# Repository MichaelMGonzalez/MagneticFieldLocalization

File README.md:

# MagneticFieldLocalization
The itensities of an indoor magnetic field may be used to aid localization of a mobile robot. This repository contains all the required files for an experiment to map and localize this field.

| Task | Status | Priority |Comments | Next Steps
| ---  | ---    | ---      | ---     | ---
| **3D CAD**
| 3D Phone Model | In-Progress | Medium | Test Model Printed | Re-print larger model
| 3D IR Wheel Encoder Model | In-Progress | Medium | Test Model Printed | Re-print larger model
| ---
| **Circuit**
| Make Board       | ORDERED     | HIGHEST | Waiting on Phone Model Test/ Schematic Verification | Solder
| Make Schemematic | Made Encoder| HIGHEST | Symbol/Phone Model Symbol/Voltage Divider | . | Label Resistor Values/Verify
| ---
| **Arduino Code**
| Main ino program    | Started | High | . | Draft
| Program Wheel Encoder | General Logic Drafted | Medium | Started to write header file| Test on hardware
| Differential Drive  | Classes made | Medium | Started to write header file| Test on hardware
| PID Controller      | Classes made | Low | . | Test on hardware
| Serial Communicator | Generation framework made | Medium | Shared Message Framework created | Lower baud rate
| ---
| **Android Code**
| GUI | Using sample code | Medium | . | Commit/Draft user flow chart
| Magnometer Sensor API | In-Progress | High | . | Read through API's
| Serial Communicator | External API's tested | High | Shared Message Framework created | Lower baud rate
| Localizer | Not Started | Very High | Depends on most everything else before we can begin | Finish everything else
| Network Module | Not Started | Medium/Low | It would be really nice to have some way to control the robot from a computer | ?
| ---
| **Python Data Viewers**
| Histogram Plotter | Made Script to plot velocities | Low | . | Generalize?
| Scatter Plot | Made Script to plot sensor voltages | Low | . | Generalize?
| ---

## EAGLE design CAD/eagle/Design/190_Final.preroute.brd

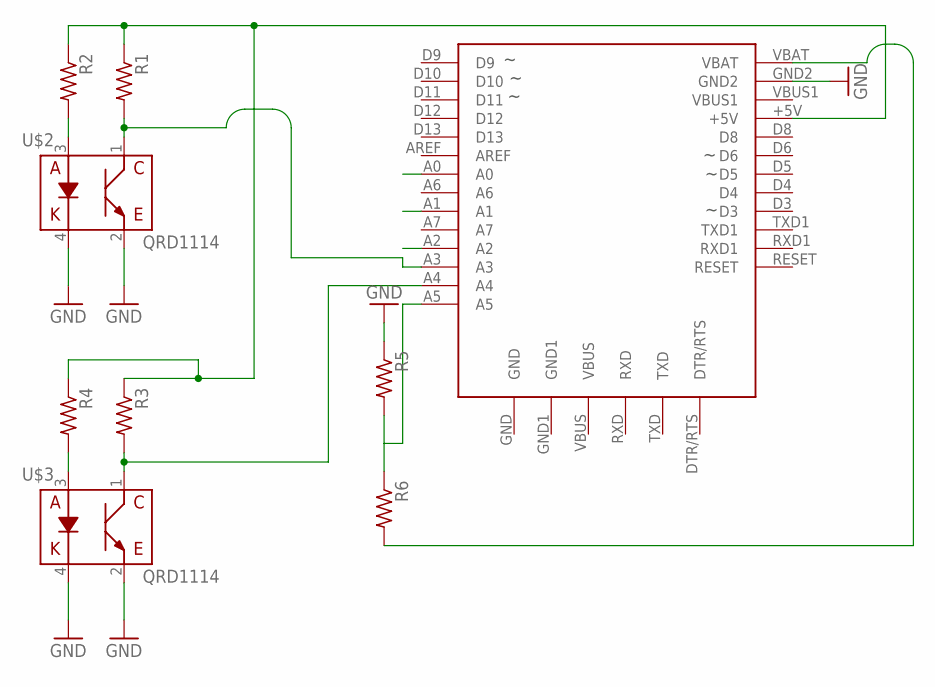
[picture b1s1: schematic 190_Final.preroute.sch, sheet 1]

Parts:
R1, R2, R3, R4, R5, R6: R-US_0204/7; 0204/7
U1_0_BRAIN: ADAFRUIT-PRO-TRINKET-5V-BOB; ADAFRUIT-PRO-TRINKET-5V
U$2, U$3: QRD1114

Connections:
+5V_0_BRAIN: R1.1, R2.1, R3.1, R4.1, U1_0_BRAIN.+5V; also elsewhere on the board
A0_0_BRAIN: U1_0_BRAIN.A0; also elsewhere on the board
A1_0_BRAIN: U1_0_BRAIN.A1; also elsewhere on the board
A2_0_BRAIN: U1_0_BRAIN.A2; also elsewhere on the board
A3_0_BRAIN: R1.2, U1_0_BRAIN.A3, U$2.1 (E)
A4_0_BRAIN: R3.2, U1_0_BRAIN.A4, U$3.1 (E)
A5_0_BRAIN: R5.2, R6.1, U1_0_BRAIN.A5
A6_0_BRAIN: U1_0_BRAIN.A6
A7_0_BRAIN: U1_0_BRAIN.A7
AREF_0_BRAIN: U1_0_BRAIN.AREF
D3_0_BRAIN: U1_0_BRAIN.D3; also elsewhere on the board
D4_0_BRAIN: U1_0_BRAIN.D4; also elsewhere on the board
D5_0_BRAIN: U1_0_BRAIN.D5; also elsewhere on the board
D6_0_BRAIN: U1_0_BRAIN.D6; also elsewhere on the board
D8_0_BRAIN: U1_0_BRAIN.D8; also elsewhere on the board
D9_0_BRAIN: U1_0_BRAIN.D9; also elsewhere on the board
D10_0_BRAIN: U1_0_BRAIN.D10; also elsewhere on the board
D11_0_BRAIN: U1_0_BRAIN.D11; also elsewhere on the board
D12_0_BRAIN: U1_0_BRAIN.D12; also elsewhere on the board
D13_0_BRAIN: U1_0_BRAIN.D13; also elsewhere on the board
DTR/RTS_0_BRAIN: U1_0_BRAIN.DTR/RTS
GND_0_BRAIN: R5.1, U1_0_BRAIN.GND, U1_0_BRAIN.GND1, U1_0_BRAIN.GND2, U$2.2 (C), U$2.4 (K), U$3.2 (C), U$3.4 (K); also elsewhere on the board
unnamed: R2.2, U$2.3 (A)
unnamed: R4.2, U$3.3 (A)
POS_1_BATTERY: R6.2, U1_0_BRAIN.VBAT; also elsewhere on the board
RESET_0_BRAIN: U1_0_BRAIN.RESET
RXD1_0_BRAIN: U1_0_BRAIN.RXD1
RXD_0_BRAIN: U1_0_BRAIN.RXD
TXD1_0_BRAIN: U1_0_BRAIN.TXD1
TXD_0_BRAIN: U1_0_BRAIN.TXD
VBUS1_0_BRAIN: U1_0_BRAIN.VBUS1
VBUS_0_BRAIN: U1_0_BRAIN.VBUS

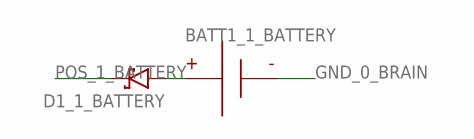
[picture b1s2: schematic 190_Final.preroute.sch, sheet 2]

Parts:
BATT1_1_BATTERY: BATTERY-9V-VERTICAL; BATTERY_9V_KEYSTONE_968
D1_1_BATTERY: RESOLVED-DIODE-SCHOTTKY_TH-DO-41-AND-DO-204AL; DIOAD1125W78L520D270_HS; MPN 1N5817

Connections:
GND_0_BRAIN: BATT1_1_BATTERY.N; also elsewhere on the board
unnamed: BATT1_1_BATTERY.P, D1_1_BATTERY.A
POS_1_BATTERY: D1_1_BATTERY.C; also elsewhere on the board

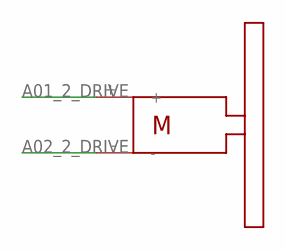
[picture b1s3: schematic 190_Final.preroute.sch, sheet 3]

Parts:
R_2_DRIVE: SOLARBOTICS_GM2; SOLARBOTICS_G2

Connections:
A01_2_DRIVE: R_2_DRIVE.+; also elsewhere on the board
A02_2_DRIVE: R_2_DRIVE.-; also elsewhere on the board

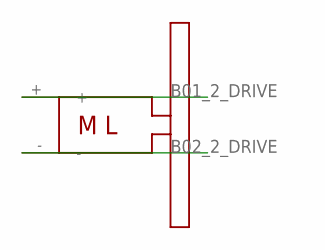
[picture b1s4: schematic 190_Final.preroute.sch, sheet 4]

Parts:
L_2_DRIVE: SOLARBOTICS_GM2_LEFT; SOLARBOTICS_G2_LEFT

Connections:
B01_2_DRIVE: L_2_DRIVE.+; also elsewhere on the board
B02_2_DRIVE: L_2_DRIVE.-; also elsewhere on the board

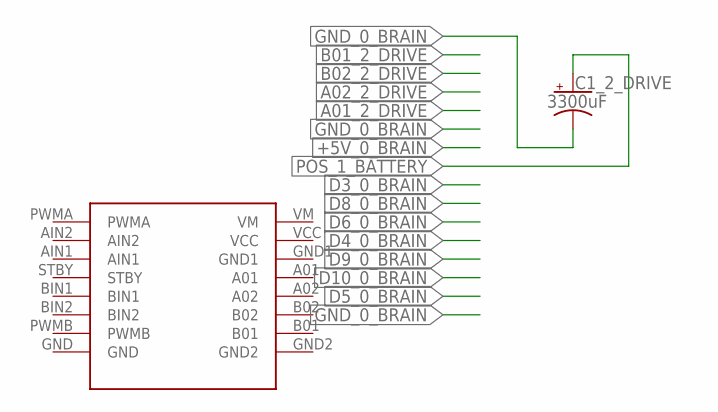
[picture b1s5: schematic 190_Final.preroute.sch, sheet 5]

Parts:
C1_2_DRIVE: 3300uF; CAPPRD750W80D1600H2200P; MPN ECA-1EM332
DRVR_2_DRIVE: SPARKFUN_DUAL_MOTOR_DRIVER-BOB; SPARKFUN_DUAL_MOTOR_DRIVER

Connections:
+5V_0_BRAIN: DRVR_2_DRIVE.VCC; also elsewhere on the board
A01_2_DRIVE: DRVR_2_DRIVE.A01; also elsewhere on the board
A02_2_DRIVE: DRVR_2_DRIVE.A02; also elsewhere on the board
B01_2_DRIVE: DRVR_2_DRIVE.B01; also elsewhere on the board
B02_2_DRIVE: DRVR_2_DRIVE.B02; also elsewhere on the board
D3_0_BRAIN: DRVR_2_DRIVE.PWMA; also elsewhere on the board
D4_0_BRAIN: DRVR_2_DRIVE.STBY; also elsewhere on the board
D5_0_BRAIN: DRVR_2_DRIVE.PWMB; also elsewhere on the board
D6_0_BRAIN: DRVR_2_DRIVE.AIN1; also elsewhere on the board
D8_0_BRAIN: DRVR_2_DRIVE.AIN2; also elsewhere on the board
D9_0_BRAIN: DRVR_2_DRIVE.BIN1; also elsewhere on the board
D10_0_BRAIN: DRVR_2_DRIVE.BIN2; also elsewhere on the board
GND_0_BRAIN: C1_2_DRIVE.2 (-), DRVR_2_DRIVE.GND, DRVR_2_DRIVE.GND1, DRVR_2_DRIVE.GND2; also elsewhere on the board
POS_1_BATTERY: C1_2_DRIVE.1 (+), DRVR_2_DRIVE.VM; also elsewhere on the board

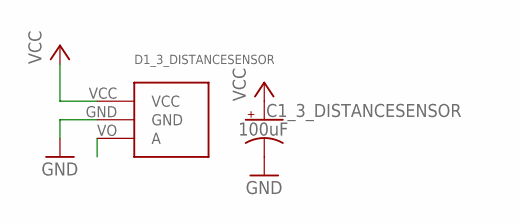
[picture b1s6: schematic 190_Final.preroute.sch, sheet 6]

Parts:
C1_3_DISTANCESENSOR: 100uF; CAPPRD250W80D630H1220P; MPN ECA-1EM101
D1_3_DISTANCESENSOR: ANALOG_DISTANCE_SENSOR-GLUE; ANALOG_DISTANCE_SENSOR_GLUE_MOUNT

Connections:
+5V_0_BRAIN: C1_3_DISTANCESENSOR.1 (+), D1_3_DISTANCESENSOR.VCC; also elsewhere on the board
A0_0_BRAIN: D1_3_DISTANCESENSOR.VO (A); also elsewhere on the board
GND_0_BRAIN: C1_3_DISTANCESENSOR.2 (-), D1_3_DISTANCESENSOR.GND; also elsewhere on the board

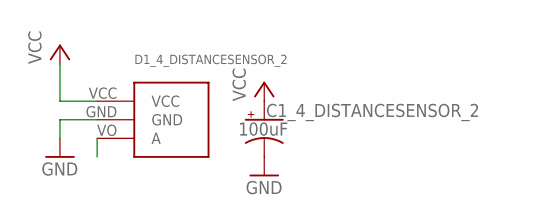
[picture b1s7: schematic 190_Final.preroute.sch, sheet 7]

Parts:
C1_4_DISTANCESENSOR_2: 100uF; CAPPRD250W80D630H1220P; MPN ECA-1EM101
D1_4_DISTANCESENSOR_2: ANALOG_DISTANCE_SENSOR-GLUE; ANALOG_DISTANCE_SENSOR_GLUE_MOUNT

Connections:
+5V_0_BRAIN: C1_4_DISTANCESENSOR_2.1 (+), D1_4_DISTANCESENSOR_2.VCC; also elsewhere on the board
A1_0_BRAIN: D1_4_DISTANCESENSOR_2.VO (A); also elsewhere on the board
GND_0_BRAIN: C1_4_DISTANCESENSOR_2.2 (-), D1_4_DISTANCESENSOR_2.GND; also elsewhere on the board

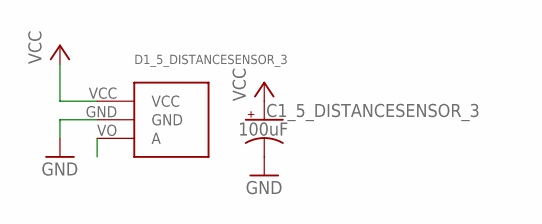
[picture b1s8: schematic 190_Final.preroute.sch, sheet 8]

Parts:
C1_5_DISTANCESENSOR_3: 100uF; CAPPRD250W80D630H1220P; MPN ECA-1EM101
D1_5_DISTANCESENSOR_3: ANALOG_DISTANCE_SENSOR-GLUE; ANALOG_DISTANCE_SENSOR_GLUE_MOUNT

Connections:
+5V_0_BRAIN: C1_5_DISTANCESENSOR_3.1 (+), D1_5_DISTANCESENSOR_3.VCC; also elsewhere on the board
A2_0_BRAIN: D1_5_DISTANCESENSOR_3.VO (A); also elsewhere on the board
GND_0_BRAIN: C1_5_DISTANCESENSOR_3.2 (-), D1_5_DISTANCESENSOR_3.GND; also elsewhere on the board

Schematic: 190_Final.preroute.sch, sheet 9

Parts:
U1_6_CASTER: CASTERADAFRUIT-3/4IN; ADAFRUIT-3/4IN-CASTER

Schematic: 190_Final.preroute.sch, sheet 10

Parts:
U1_7_CASTER_2: CASTERADAFRUIT-3/4IN; ADAFRUIT-3/4IN-CASTER

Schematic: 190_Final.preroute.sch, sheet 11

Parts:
LED1_8_LED: LED5MM
R1_8_LED: 330; RESAD770W45L370D210_HS; MPN CFR-12JB-52-330R

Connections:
D11_0_BRAIN: LED1_8_LED.A; also elsewhere on the board
GND_0_BRAIN: R1_8_LED.2; also elsewhere on the board
unnamed: LED1_8_LED.K (C), R1_8_LED.1

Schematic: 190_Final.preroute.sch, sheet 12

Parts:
LED1_9_LED_2: LED5MM
R1_9_LED_2: 330; RESAD770W45L370D210_HS; MPN CFR-12JB-52-330R

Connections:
D12_0_BRAIN: LED1_9_LED_2.A; also elsewhere on the board
GND_0_BRAIN: R1_9_LED_2.2; also elsewhere on the board
unnamed: LED1_9_LED_2.K (C), R1_9_LED_2.1

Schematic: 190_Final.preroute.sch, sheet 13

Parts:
B1_10_BUTTON: BUTTON-TACTILE-ROUND; BUTTON-TACTILE-ROUND-ADAFRUIT1009

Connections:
D13_0_BRAIN: B1_10_BUTTON.P; also elsewhere on the board
GND_0_BRAIN: B1_10_BUTTON.S; also elsewhere on the board

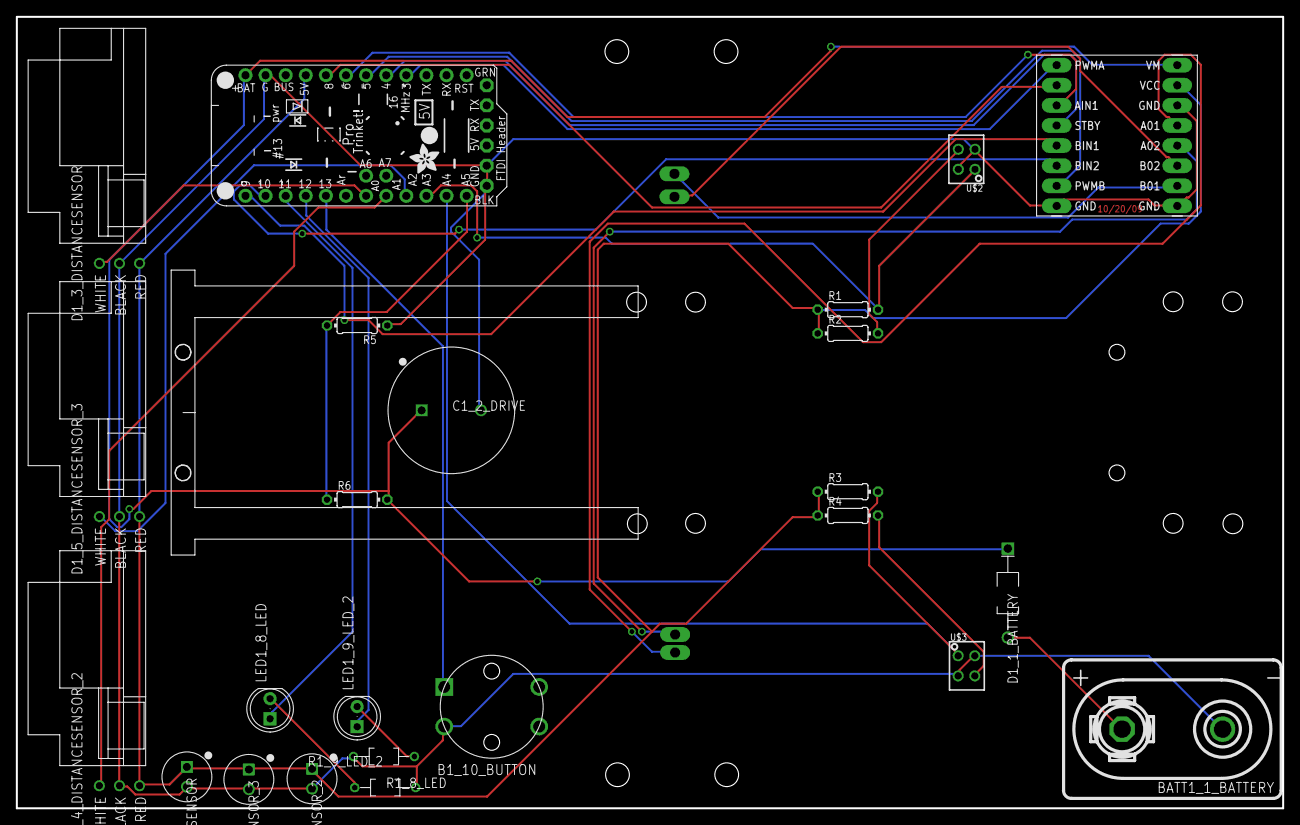
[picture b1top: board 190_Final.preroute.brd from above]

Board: 2 copper layers, 160.0 x 100.0 mm, 30 parts (0 on the bottom side), 28 nets.

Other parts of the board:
U$1: PHONE_STAND
U$4: IRSTAND

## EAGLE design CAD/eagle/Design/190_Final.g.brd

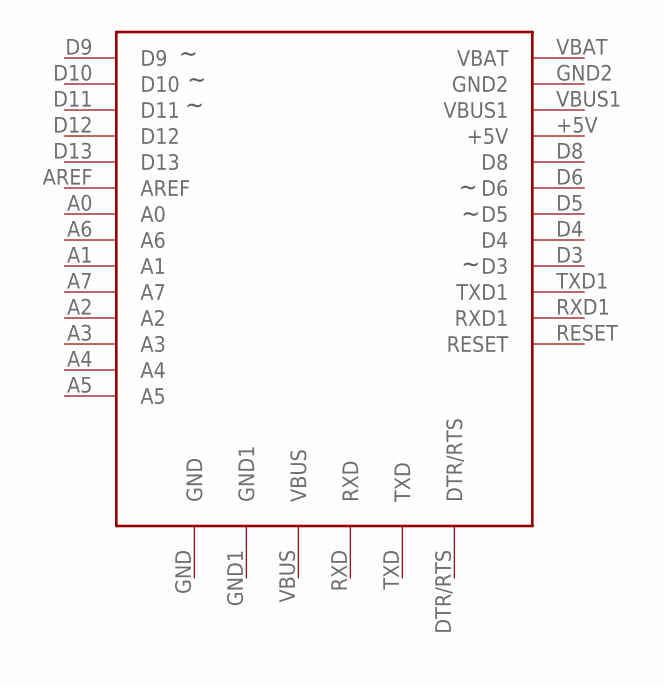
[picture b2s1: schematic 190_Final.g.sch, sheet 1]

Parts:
U1_0_brain: ADAFRUIT-PRO-TRINKET-5V-BOB; ADAFRUIT-PRO-TRINKET-5V

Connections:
+5V_0_brain: U1_0_brain.+5V; also elsewhere on the board
A0_0_brain: U1_0_brain.A0; also elsewhere on the board
A1_0_brain: U1_0_brain.A1; also elsewhere on the board
A2_0_brain: U1_0_brain.A2; also elsewhere on the board
A3_0_brain: U1_0_brain.A3
A4_0_brain: U1_0_brain.A4
A5_0_brain: U1_0_brain.A5
A6_0_brain: U1_0_brain.A6
A7_0_brain: U1_0_brain.A7
AREF_0_brain: U1_0_brain.AREF
D3_0_brain: U1_0_brain.D3; also elsewhere on the board
D4_0_brain: U1_0_brain.D4; also elsewhere on the board
D5_0_brain: U1_0_brain.D5; also elsewhere on the board
D6_0_brain: U1_0_brain.D6; also elsewhere on the board
D8_0_brain: U1_0_brain.D8; also elsewhere on the board
D9_0_brain: U1_0_brain.D9; also elsewhere on the board
D10_0_brain: U1_0_brain.D10; also elsewhere on the board
D11_0_brain: U1_0_brain.D11; also elsewhere on the board
D12_0_brain: U1_0_brain.D12; also elsewhere on the board
D13_0_brain: U1_0_brain.D13; also elsewhere on the board
DTR/RTS_0_brain: U1_0_brain.DTR/RTS
GND_0_brain: U1_0_brain.GND, U1_0_brain.GND1, U1_0_brain.GND2; also elsewhere on the board
POS_1_battery: U1_0_brain.VBAT; also elsewhere on the board
RESET_0_brain: U1_0_brain.RESET
RXD1_0_brain: U1_0_brain.RXD1
RXD_0_brain: U1_0_brain.RXD
TXD1_0_brain: U1_0_brain.TXD1
TXD_0_brain: U1_0_brain.TXD
VBUS1_0_brain: U1_0_brain.VBUS1
VBUS_0_brain: U1_0_brain.VBUS

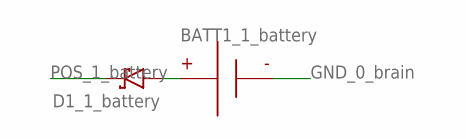
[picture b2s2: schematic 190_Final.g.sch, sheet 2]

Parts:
BATT1_1_battery: BATTERY-9V-VERTICAL; BATTERY_9V_KEYSTONE_968

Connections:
GND_0_brain: BATT1_1_battery.N; also elsewhere on the board

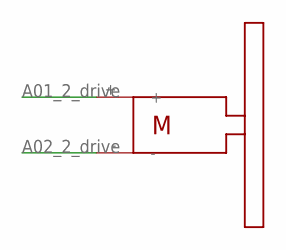
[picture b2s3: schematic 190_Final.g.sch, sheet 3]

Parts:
R_2_drive: SOLARBOTICS_GM2; SOLARBOTICS_G2

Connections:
A01_2_drive: R_2_drive.+; also elsewhere on the board
A02_2_drive: R_2_drive.-; also elsewhere on the board

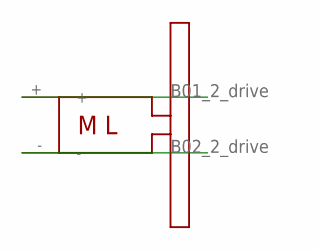
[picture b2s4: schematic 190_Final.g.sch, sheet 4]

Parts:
L_2_drive: SOLARBOTICS_GM2_LEFT; SOLARBOTICS_G2_LEFT

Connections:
B01_2_drive: L_2_drive.+; also elsewhere on the board
B02_2_drive: L_2_drive.-; also elsewhere on the board

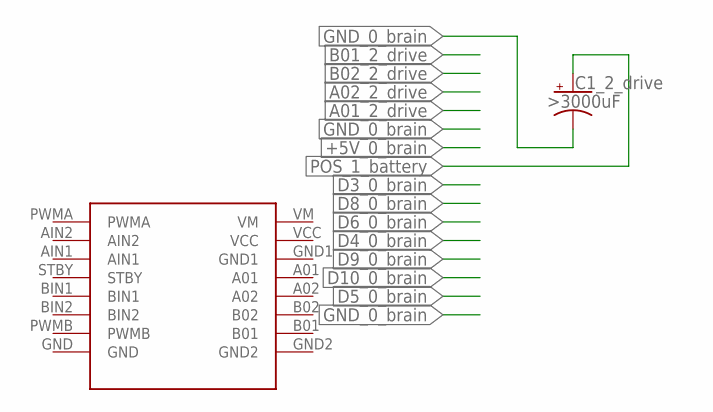
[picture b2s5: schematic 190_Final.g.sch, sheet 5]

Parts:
DRVR_2_drive: SPARKFUN_DUAL_MOTOR_DRIVER-BOB; SPARKFUN_DUAL_MOTOR_DRIVER

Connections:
+5V_0_brain: DRVR_2_drive.VCC; also elsewhere on the board
A01_2_drive: DRVR_2_drive.A01; also elsewhere on the board
A02_2_drive: DRVR_2_drive.A02; also elsewhere on the board
B01_2_drive: DRVR_2_drive.B01; also elsewhere on the board
B02_2_drive: DRVR_2_drive.B02; also elsewhere on the board
D3_0_brain: DRVR_2_drive.PWMA; also elsewhere on the board
D4_0_brain: DRVR_2_drive.STBY; also elsewhere on the board
D5_0_brain: DRVR_2_drive.PWMB; also elsewhere on the board
D6_0_brain: DRVR_2_drive.AIN1; also elsewhere on the board
D8_0_brain: DRVR_2_drive.AIN2; also elsewhere on the board
D9_0_brain: DRVR_2_drive.BIN1; also elsewhere on the board
D10_0_brain: DRVR_2_drive.BIN2; also elsewhere on the board
GND_0_brain: DRVR_2_drive.GND, DRVR_2_drive.GND1, DRVR_2_drive.GND2; also elsewhere on the board
POS_1_battery: DRVR_2_drive.VM; also elsewhere on the board

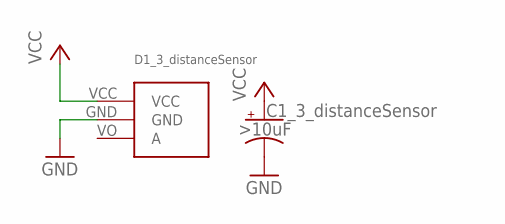
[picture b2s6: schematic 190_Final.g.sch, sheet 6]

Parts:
D1_3_distanceSensor: ANALOG_DISTANCE_SENSOR-GLUE; ANALOG_DISTANCE_SENSOR_GLUE_MOUNT

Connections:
+5V_0_brain: D1_3_distanceSensor.VCC; also elsewhere on the board
A0_0_brain: D1_3_distanceSensor.VO (A); also elsewhere on the board
GND_0_brain: D1_3_distanceSensor.GND; also elsewhere on the board

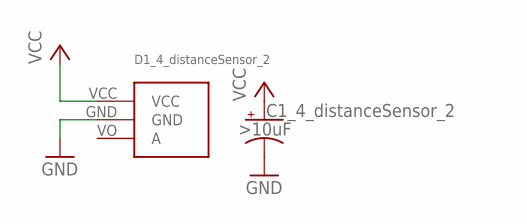
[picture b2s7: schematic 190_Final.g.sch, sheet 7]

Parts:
D1_4_distanceSensor_2: ANALOG_DISTANCE_SENSOR-GLUE; ANALOG_DISTANCE_SENSOR_GLUE_MOUNT

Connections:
+5V_0_brain: D1_4_distanceSensor_2.VCC; also elsewhere on the board
A1_0_brain: D1_4_distanceSensor_2.VO (A); also elsewhere on the board
GND_0_brain: D1_4_distanceSensor_2.GND; also elsewhere on the board

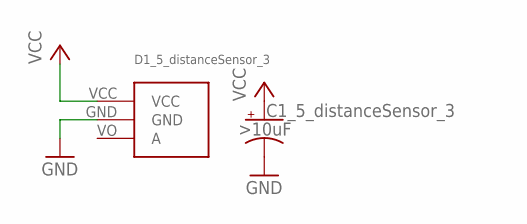
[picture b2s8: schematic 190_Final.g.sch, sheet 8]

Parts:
D1_5_distanceSensor_3: ANALOG_DISTANCE_SENSOR-GLUE; ANALOG_DISTANCE_SENSOR_GLUE_MOUNT

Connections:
+5V_0_brain: D1_5_distanceSensor_3.VCC; also elsewhere on the board
A2_0_brain: D1_5_distanceSensor_3.VO (A); also elsewhere on the board
GND_0_brain: D1_5_distanceSensor_3.GND; also elsewhere on the board

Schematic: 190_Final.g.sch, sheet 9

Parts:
u1_6_caster: CASTERADAFRUIT-3/4IN; ADAFRUIT-3/4IN-CASTER

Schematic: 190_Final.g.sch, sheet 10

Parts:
u1_7_caster_2: CASTERADAFRUIT-3/4IN; ADAFRUIT-3/4IN-CASTER

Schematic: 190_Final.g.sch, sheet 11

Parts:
LED1_8_led: LED5MM

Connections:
D11_0_brain: LED1_8_led.A; also elsewhere on the board

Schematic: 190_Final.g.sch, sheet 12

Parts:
LED1_9_led_2: LED5MM

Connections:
D12_0_brain: LED1_9_led_2.A; also elsewhere on the board

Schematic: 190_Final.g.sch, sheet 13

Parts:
B1_10_button: BUTTON-TACTILE-ROUND; BUTTON-TACTILE-ROUND-ADAFRUIT1009

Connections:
D13_0_brain: B1_10_button.P; also elsewhere on the board
GND_0_brain: B1_10_button.S; also elsewhere on the board

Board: 2 copper layers, 13 parts (0 on the bottom side), 20 nets, no tracks yet.

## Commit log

2016-05-18 starting
2016-05-18 commenting and generated dxf
2016-05-18 started eagle draft
2016-05-19 Made a folder for 3D parts, added encoder mount
2016-05-20 made lbrackets
2016-05-20 More openscad practice
2016-05-20 3d motor bracket
2016-05-20 removed some material from motor bracket
2016-05-20 removed old motor file
2016-05-24 Added design files
2016-05-24 updated phone case
2016-05-24 caught a nasty electric bug
2016-05-24 more electrical bug catches
2016-05-24 updated 3d parts eagle lib
2016-05-24 Updated 3d phone bracket with more accurate extruder widths
2016-05-24 cleaning dirs, added gerbers
2016-05-24 More cleaning
2016-05-24 Removed stl files, git ignores them now
2016-05-25 made clean targets stronger
2016-05-25 Started serial mesenger
2016-05-25 defined a bunch of message types
2016-05-25 Added priorities to readme
2016-05-25 typos
2016-05-25 added message size element
2016-05-25 Wrote PIDController draft
2016-05-25 fixed pid bug, made tester/plotter
2016-05-26 made pid tests smoother
2016-05-26 refactored odometer, started making it into a class
2016-05-26 updated PID sim to be more realistic with oscillation
2016-05-26 removed machine generated code
2016-05-26 gerbers updated, ready to fab
2016-05-28 made 3d models follow better OO design
2016-05-28 removed machine generated files
2016-05-28 Added LPKF build target for gerbers
2016-05-28 3D parts libraries doesn't place outlines on layer 20 anymore
2016-05-28 Updated design to use library updates
2016-05-28 Made PID simulator play nicer with git
2016-05-29 writing key/vals to java
2016-05-30 made lists for serial communicator
2016-05-30 made lpkf design nicer for board mill
2016-05-31 Updated make files/lpkf board
2016-06-01 Added differential drive draft
2016-06-01 Made robot meta info files/unit conversion files/updated readme
2016-06-01 made keywords.txt
2016-06-01 massive refactor
2016-06-01 started ino
2016-06-01 auto generated starter code
2016-06-01 Defined encoder.cpp file
2016-06-01 Added more structure to main ino
2016-06-05 Android
    Started Android - starting sensor API
2016-06-05 Differential drive can say what speed wheels should operate at
2016-06-05 Android magnetometer
    Is displaying Magnetometer values (magnitude of vector) from the
    calibrated magnetic filed sensor type. Starting Timer class.
2016-06-06 More Android
    Added xyz axis readings to the display. Rounded values to 3 decimal
    places
2016-06-06 Android Timestamp
    Time and Magnetometer displays completed
2016-06-06 Android studio meta files
    Should git ignore these?
2016-06-06 Refactored serial communicator, working on new odom models
2016-06-06 John Doe is Ashley Perez
    My name is not John Doe. Timer class deleted, it ended up not being
    necessary.
2016-06-06 more data crunching
2016-06-06 Arduino odometry library works!
2016-06-06 PID Controller works!
2016-06-06 Found a way to write serial in python
2016-06-06 python communicator can pick good inputs to read
2016-06-06 Serial communicator python script has been transformed to a class
2016-06-06 Communicator works on linux
2016-06-06 CSV
    CSV file is being saved in Downloads folder.
2016-06-06 Updated serial write
2016-06-06 Android - Multiple files
    Creates a new file every time the start log button is pressed.
2016-06-07 PID seems relatively smooth, tons of serial debugging
2016-06-07 Logger Class
    Added Logger class
2016-06-07 PID tests reproducable
2016-06-07 Added SerialConverter class
2016-06-07 PID Qlearning
2016-06-07 removed binaries
2016-06-07 Serial communicator testing framework update
2016-06-07 Made visualization cleaner
2016-06-07 Finished Serial Converter
2016-06-07 new pd gets sent via serial
2016-06-07 QLerner can reload old states
2016-06-07 Retook phone measurements, playing with makerbot settings
2016-06-07 QLearning experiment is running!
2016-06-08 fine tuned encoder thresholds
2016-06-08 MAGNETIC FIELD DATA
2016-06-08 Accelerometer added
2016-06-08 Trying to change file save loc
2016-06-08 Accel data not looking good, Mag looking fantastic
2016-06-11 overdue commits
2016-06-23 Added state machine to robot
2016-06-23 Refactoring mainactivity
2016-06-23 Changed main activity layout
2016-06-24 Implemented hlsm
2016-06-24 Decoupling control from main activity
2016-06-24 uncommited changes from last commit
2016-06-24 Networking module, filtered accelerometer data
2016-06-25 Added movement control hlsm
2016-06-27 Basic serial state machine added
2016-06-27 Serial connects automatically
2016-06-27 Made setip dialog
2016-06-27 refactoring, added fileIO
2016-06-27 IP saving in
2016-08-07 Create LICENSE

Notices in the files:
parts and their libraries:
SparkFun-Sensors: Licensing: Creative Commons ShareAlike 4.0 International - https://creativecommons.org/licenses/by-sa/4.0
